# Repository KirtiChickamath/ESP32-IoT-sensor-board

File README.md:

# ESP32 IoT Sensor Board

A 4-layer IoT PCB designed in KiCad 9 as part of the **Advanced PCB Design with KiCad 9** course by Dr. Peter Dalmaris.

## Overview

This board is a medium-complexity IoT development platform built around the ESP32-C3 microcontroller. It includes power management, wireless connectivity, storage, and environmental sensing. All on a compact 4-layer PCB.

## Features

- ESP32-C3-WROOM-02 — WiFi and Bluetooth
- USB-C input with ESD protection (USBLC6) and polyfuse
- LiPo battery management with power-path (MCP73871)
- 3.3V LDO voltage regulator (LM1117)
- USB-to-UART bridge (CP2102N) for programming and debugging
- SPI flash memory (W25Q32)
- MicroSD card slot (SPI mode)
- BME280 — temperature, humidity, and pressure (I2C)
- Ambient light sensor (TEMT6000)
- Microphone with preamplifier (MAX4466)
- Status LEDs — power good, charging, charged
- Boot and EN tactile switches
- GPIO and I2C breakout header
- Test points for SPI signals

## Layer Stackup

 Layer - Purpose 

 Top copper - L1 -  Components and signal routing 
 Inner 1 - L2 - Ground plane 
 Inner 2 - L3 - 3.3V power plane 
 Bottom copper - L4 -  Additional signal routing 

## Communication Interfaces

 Interface - Connected To 

 SPI - Flash memory, SD card 
 I2C - BME280, OLED header 
 UART - CP2102N (via USB) 
 ADC - Light sensor, microphone 

## Schematic

---

## PCB Layout

## 3D View

## Tools Used

- KiCad 
- HQDFM

---

## Course Reference

**Advanced PCB Design with KiCad 9**  
Instructor: Dr. Peter Dalmaris  
Platform: Udemy

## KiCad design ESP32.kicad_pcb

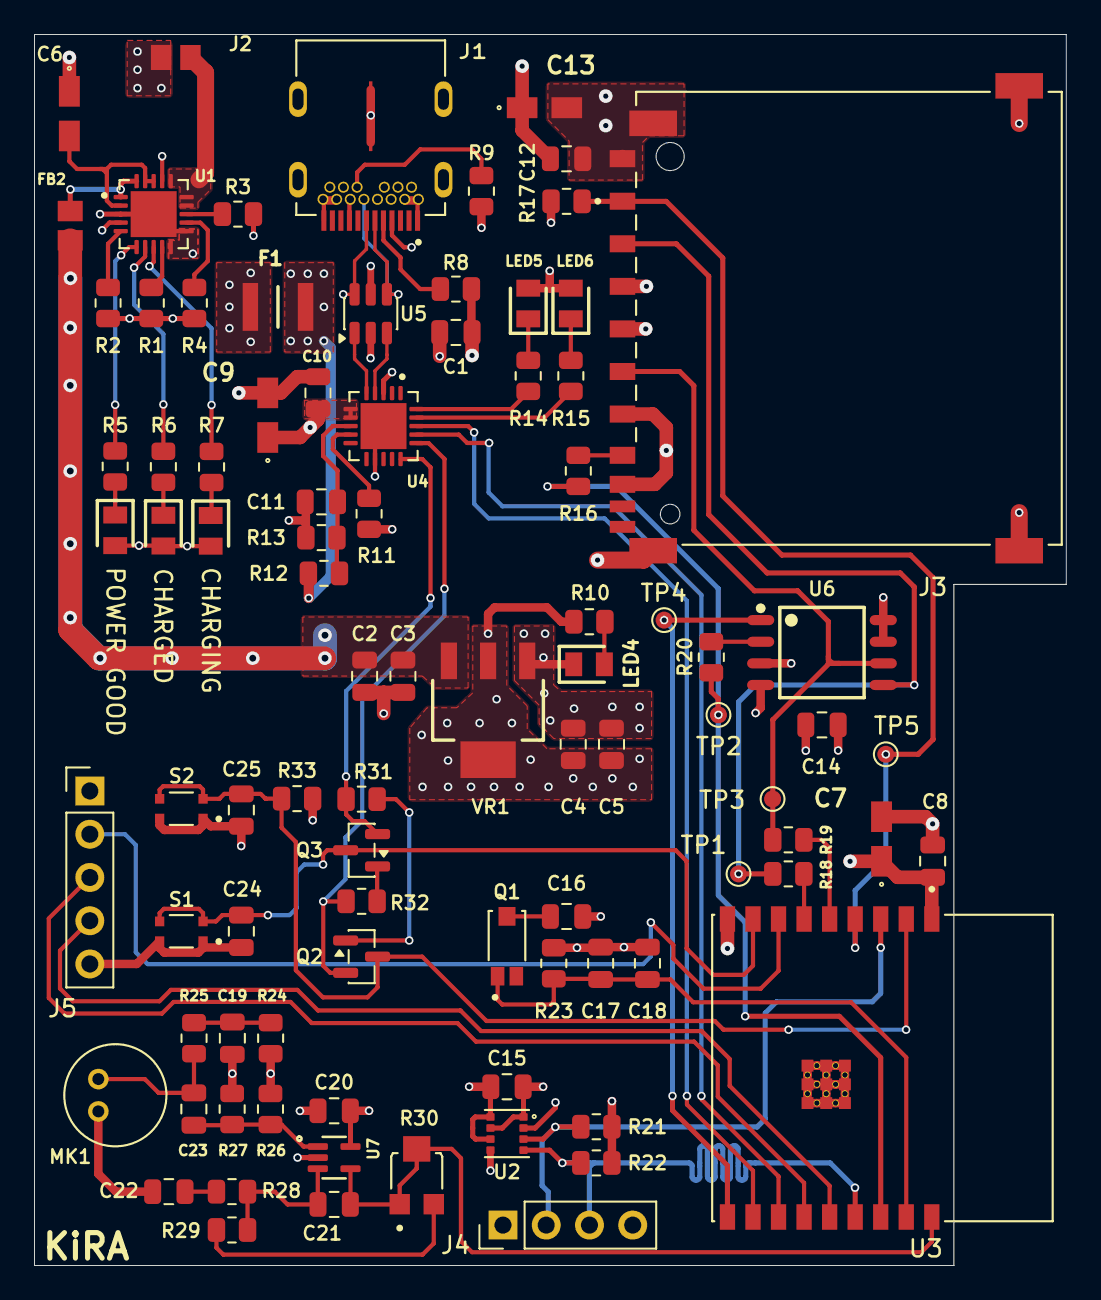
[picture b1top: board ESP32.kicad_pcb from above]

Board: 4 copper layers, 60.6 x 72.3 mm, 90 parts (0 on the bottom side), 62 nets.

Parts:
C1, C2, C5, C8, C10, C12, C14, C15, C16, C19, C20, C24: 100nF; C_0805_2012Metric
C3, C4, C22: 10uF; C_0805_2012Metric
C6, C9: 4.7uF; T491A
C7, C13: 10uF; T491A
C11, C25: 1uF; C_0805_2012Metric
C17, C18, C23: 10nF; C_0805_2012Metric
C21: 100pF; C_0805_2012Metric
F1: 0ZCH0110AF2E; FUSC3226X100N
FB2: FBMJ2125HM330-T; BEADC2012X105N
J1: SS-52400-002; BELFUSE_SS-52400-002
J2: B2B-PH-SM4-TB; BEADC2012X105N
J3: GSD090012SEU; AMPHENOL_GSD090012SEU
J4: Conn_01x04_Pin; PinHeader_1x04_P2.54mm_Vertical
J5: Conn_01x05_Pin; PinHeader_1x05_P2.54mm_Vertical
LED1, LED5: LTST-C170GKT; LEDC2012X120N
LED2, LED4, LED6: LTST-C170KRKT; LEDC2012X120N
LED3: LTST-C170TBKT; LEDC2012X120N
MK1: CMC-5042PF-AC; CUI_CMC-5042PF-AC
Q1: TEMT6000X01; TRANS_TEMT6000X01
Q2, Q3: BC817; SOT-23
R1, R2, R17, R23, R31, R32, R33: 10K; R_0805_2012Metric
R3, R24, R25: 2K; R_0805_2012Metric
R4: 20K; R_0805_2012Metric
R5, R6, R7, R10, R14, R15: 470R; R_0805_2012Metric
R8, R9: 5K1; R_0805_2012Metric
R11, R28: 1K; R_0805_2012Metric
R12: 22K1; R_0805_2012Metric
R13: 47K5; R_0805_2012Metric
R16, R18, R19, R20: 50R; R_0805_2012Metric
R21, R22: 4K7; R_0805_2012Metric
R26, R27: 1M; R_0805_2012Metric
R29: 22K; R_0805_2012Metric
R30: 35WR100KLFTR; TRIM_35WR100KLFTR
S1: BOOT; SW_USLPT2819DT2TR
S2: RESET; SW_USLPT2819DT2TR
TP1: Test MOSI; TestPoint_Pad_D1.0mm
TP2: Test MISO; TestPoint_Pad_D1.0mm
TP3: Test SCLK; TestPoint_Pad_D1.0mm
TP4: Test CS; TestPoint_Pad_D1.0mm
TP5: Test CS_SD; TestPoint_Pad_D1.0mm
U1: MCP73871-2CAI_ML; QFN50P400X400X100-21N
U2: BME280; PSON65P250X250X100-8N
U3: ESP32-C3-WROOM-02-H4; MODULE_ESP32-C3-WROOM-02-H4
U4: CP2102N-Axx-xQFN20; QFN50P400X400X100-21N
U5: USBLC6-2SC6; SOT-23-6
U6: W25Q32JVSSIQ; SOIC127P790X216-8N
U7: MAX4466EXK; SOT65P210X110-5N
VR1: LM1117MPX-3.3; VREG_LM1117MPX-3.3

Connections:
+3.3V: C4.1, C5.1, C7.1, C8.1, C9.1, C10.2, C12.1, C13.1, C14.1, C15.1, C16.1, C20.2, J3.4 (VDD1), J4.1, J5.1, LED5.2 (A), LED6.2 (A), R10.1, R11.1, R17.1, R21.2, R22.2, R24.1, R26.1, R33.2, U2.2 (CSB), U2.6 (VDDIO), U2.8 (VDD), U3.1 (3V3), U4.6 (VDD), U4.7 (VREGIN), U6.3 (~WP(IO2)), U6.7 (~HOLD/~RESET(IO3)), U6.8 (VCC), U7.5 (VCC), VR1.2 (VOUT_2), VR1.4 (VOUT_4)
+5V: C2.1, C3.1, FB2.2, VR1.3 (VIN)
/+5V_USB: F1.2, LED1.2 (A), LED2.2 (A), LED3.2 (A), U1.4 (PROG2), U1.17 (CE)
/ESP32-C3-02/BOOT: C24.1, Q3.3 (C), S1.3, S1.4, U3.8 (IO9)
/ESP32-C3-02/CS: TP4.1 (1_1), U3.10 (IO10), U6.1 (~CS)
/ESP32-C3-02/CS_SD: J3.1 (CD/DAT3), R17.2, TP5.1 (1_1), U3.4 (IO5)
/ESP32-C3-02/DTR: Q3.2 (E), R31.1, U4.15 (~CTS)
/ESP32-C3-02/EN: C25.1, Q2.3 (C), R33.1, S2.3, S2.4, U3.2 (EN)
/ESP32-C3-02/GPIO8: J5.2, U3.7 (IO8)
/ESP32-C3-02/GPIO18: J5.3, U3.13 (IO18)
/ESP32-C3-02/GPIO19: J5.4, U3.14 (IO19)
/ESP32-C3-02/MIC_OUT: C21.1, R30.1, R30.2, U3.18 (IO0), U7.4 (OUT)
/ESP32-C3-02/MISO_DO: R16.2, R20.2, TP2.1 (1_1), U3.16 (IO2)
/ESP32-C3-02/MOSI_DI: J3.2 (CMD), R18.2, TP1.1 (1_1), U6.5 (DI(IO0))
/ESP32-C3-02/PHOTO_S: C17.1, C18.1, Q1.1, R23.1, U3.17 (IO1)
/ESP32-C3-02/RTS: Q2.2 (E), R32.1, U4.16 (~RTS)
/ESP32-C3-02/RX_TX: U3.12 (TXD), U4.17 (RXD)
/ESP32-C3-02/SCL: J4.3, R22.1, U2.4 (SCK), U3.15 (IO3)
/ESP32-C3-02/SCLK: J3.5 (CLK), R19.1, TP3.1 (1_1), U6.6 (CLK)
/ESP32-C3-02/SDA: J4.2, R21.1, U2.3 (SDI), U3.3 (IO4)
/ESP32-C3-02/TX_RX: U3.11 (RXD), U4.18 (TXD)
/ESP32-C3-02/USB_DN: U4.5 (D-), U5.1 (I/O1)
/ESP32-C3-02/USB_DP: U4.4 (D+), U5.3 (I/O2)
/USB_D+: J1.A6 (DP1), J1.B6 (DP2), U5.4 (I/O2)
/USB_D-: J1.A7 (DN1), J1.B7 (DN2), U5.6 (I/O1)
/VBAT: J2.2, U1.14 (VBAT), U1.15 (VBAT), U1.16 (VBAT_SENSE)
/VBUS: C1.1, F1.1, J1.A4 (VBUSA1), J1.A9 (VBUSA2), J1.B4 (VBUSB1), J1.B9 (VBUSB2), R12.1, U5.5 (VBUS)
GND: C1.2, C2.2, C3.2, C4.2, C5.2, C6.1, C7.2, C8.2, C9.2, C10.1, C11.2, C12.2, C13.2, C14.2, C15.2, C17.2, C18.2, C19.1, C20.1, C22.1, C24.2, C25.2, J1.A1 (GNDA1), J1.A12 (GNDA2), J1.B1 (GNDB1), J1.B12 (GNDB2), J1.G1 (GND/SHIELD), J1.G2 (GND/SHIELD), J1.G3 (GND/SHIELD), J1.G4 (GND/SHIELD), J1.S1 (GND/SHIELD), J1.S2 (GND/SHIELD), J1.S3 (GND/SHIELD), J1.S4 (GND/SHIELD), J2.1, J3.3 (VSS1), J3.6 (VSS2), J3.8 (DAT1), J3.9 (DAT2), J3.G1 (SHIELD_GND), J3.G2 (SHIELD_GND), J3.G3 (SHIELD_GND), J3.G4 (SHIELD_GND), J4.4, J5.5, LED4.1 (K), MK1.GND, R1.1, R2.2, R3.2, R4.2, R8.1, R9.1, R13.2, R23.2, R27.2, S1.1, S1.2, S2.1, S2.2, U1.3 (SEL), U1.10 (VSS), U1.11 (VSS), U1.21 (VSS), U2.1 (GND), U2.5 (SDO), U2.7 (GND), U3.9 (GND), U3.19 (GND), U3.20 (GND), U3.21 (GND), U3.22 (GND), U3.23 (GND), U3.24 (GND), U3.25 (GND), U3.26 (GND), U3.27 (GND), U3.28 (GND), U3.29 (GND), U3.30 (GND), U3.31 (GND), U3.32 (GND), U3.33 (GND), U3.34 (GND), U3.35 (GND), U3.36 (GND), U3.37 (GND), U3.38 (GND), U3.39 (GND), U4.3 (GND), U4.12 (GND), U4.21 (GND), U5.2 (GND), U6.4 (GND), U7.2 (GND), VR1.1 (GND)
unnamed: C16.2, Q1.3
unnamed: C19.2, R24.2, R25.1
unnamed: C22.2, R28.2
unnamed: C23.1, MK1.OUT, R25.2
unnamed: FB2.1, U1.1 (OUT), U1.20 (OUT)
unnamed: J1.A5 (CC1), R8.2
unnamed: J1.B5 (CC2), R9.2
unnamed: J3.7 (DAT0), R16.1
unnamed: LED1.1 (K), R6.1
unnamed: LED2.1 (K), R7.1
unnamed: LED3.1 (K), R5.1
unnamed: LED4.2 (A), R10.2
unnamed: LED5.1 (K), R14.1
unnamed: LED6.1 (K), R15.1
unnamed: Q2.1 (B), R31.2
unnamed: Q3.1 (B), R32.2
unnamed: R29.2, R30.3
unnamed: R3.1, U1.13 (PROG1)
unnamed: R4.1, U1.12 (PROG3)
unnamed: R7.2, U1.8 (STAT1/~LBO)
unnamed: R6.2, U1.7 (STAT2)
unnamed: R2.1, U1.5 (THERM)
unnamed: C6.2, U1.2 (VPCC), U1.18 (IN), U1.19 (IN)
unnamed: R5.2, U1.6 (~PG)
unnamed: R1.2, U1.9 (~TE)
unnamed: R19.2, U3.5 (IO6)
unnamed: R18.1, U3.6 (IO7)
unnamed: C11.1, R12.2, R13.1, U4.8 (VBUS)
unnamed: R11.2, U4.9 (~RST)
unnamed: R15.2, U4.19 (~RXT/GPIO.3)
unnamed: R14.2, U4.20 (~TXT/GPIO.2)
unnamed: R20.1, U6.2 (DO(IO1))
unnamed: C23.2, R26.2, R27.1, U7.1 (IN+)
unnamed: C21.2, R28.1, R29.1, U7.3 (IN-)

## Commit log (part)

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2026-06-11 README.md
